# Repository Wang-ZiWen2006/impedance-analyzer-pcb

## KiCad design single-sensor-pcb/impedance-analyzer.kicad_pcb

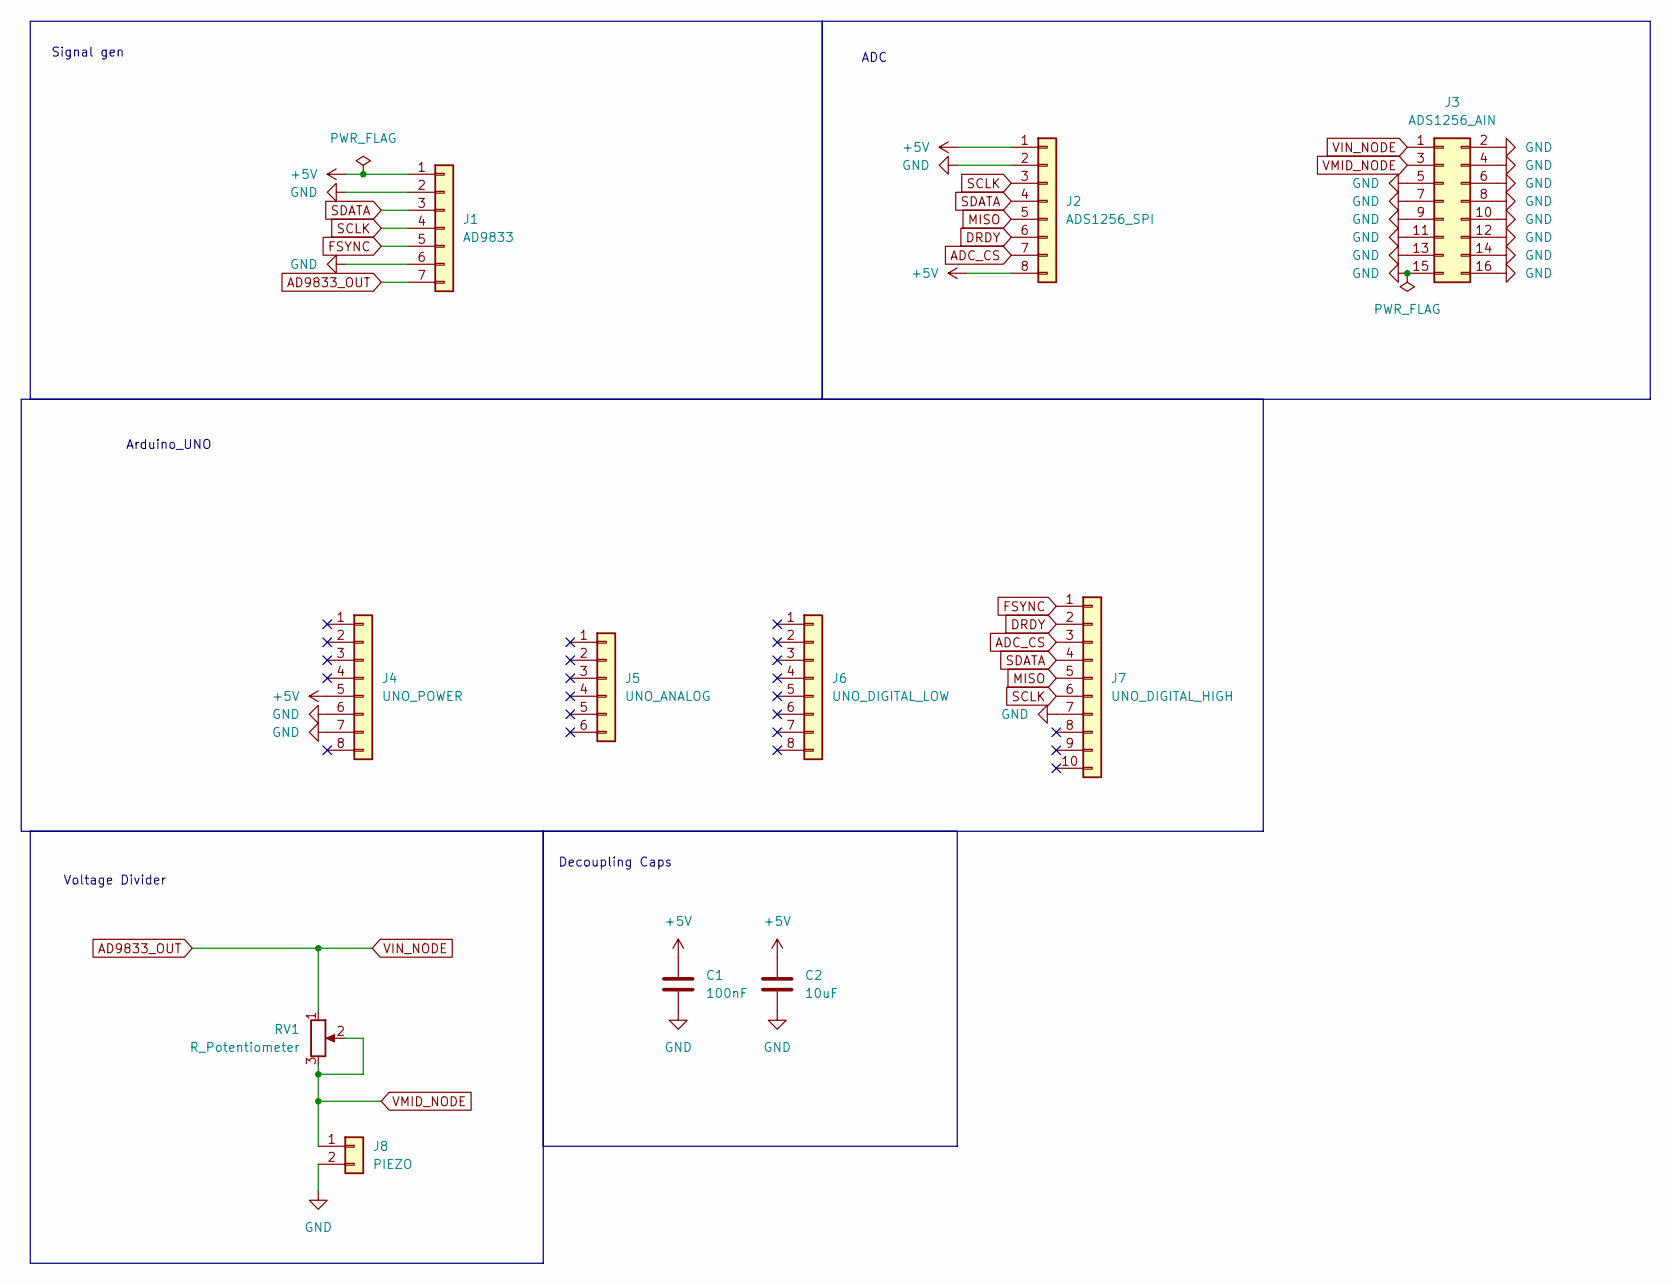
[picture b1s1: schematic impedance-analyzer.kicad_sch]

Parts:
C1: 100nF; C_Disc_D5.0mm_W2.5mm_P5.00mm
C2: 10uF; C_Disc_D5.0mm_W2.5mm_P5.00mm
J1: AD9833; PinSocket_1x07_P2.54mm_Vertical
J2: ADS1256_SPI; PinSocket_1x08_P2.54mm_Vertical
J3: ADS1256_AIN; PinSocket_2x08_P2.54mm_Vertical
J4: UNO_POWER; PinHeader_1x08_P2.54mm_Vertical
J5: UNO_ANALOG; PinHeader_1x06_P2.54mm_Vertical
J6: UNO_DIGITAL_LOW; PinHeader_1x08_P2.54mm_Vertical
J7: UNO_DIGITAL_HIGH; PinHeader_1x10_P2.54mm_Vertical
J8: PIEZO; TerminalBlock_Phoenix_MPT-0,5-2-2.54_1x02_P2.54mm_Horizontal
RV1: R_Potentiometer; Potentiometer_Bourns_3296W_Vertical

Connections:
+5V: C1.1, C2.1, J1.1, J2.1, J2.8, J4.5
AD9833_OUT: J1.7, J3.1, RV1.1
ADC_CS: J2.7, J7.3
DRDY: J2.6, J7.2
FSYNC: J1.5, J7.1
GND: C1.2, C2.2, J1.2, J1.6, J2.2, J3.2, J3.4, J3.5, J3.6, J3.7, J3.8, J3.9, J3.10, J3.11, J3.12, J3.13, J3.14, J3.15, J3.16, J4.6, J4.7, J7.7, J8.2
MISO: J2.5, J7.5
SCLK: J1.4, J2.3, J7.6
SDATA: J1.3, J2.4, J7.4
VMID_NODE: J3.3, J8.1, RV1.2, RV1.3

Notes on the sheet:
ADC
Voltage Divider
Signal gen
Decoupling Caps
Arduino_UNO

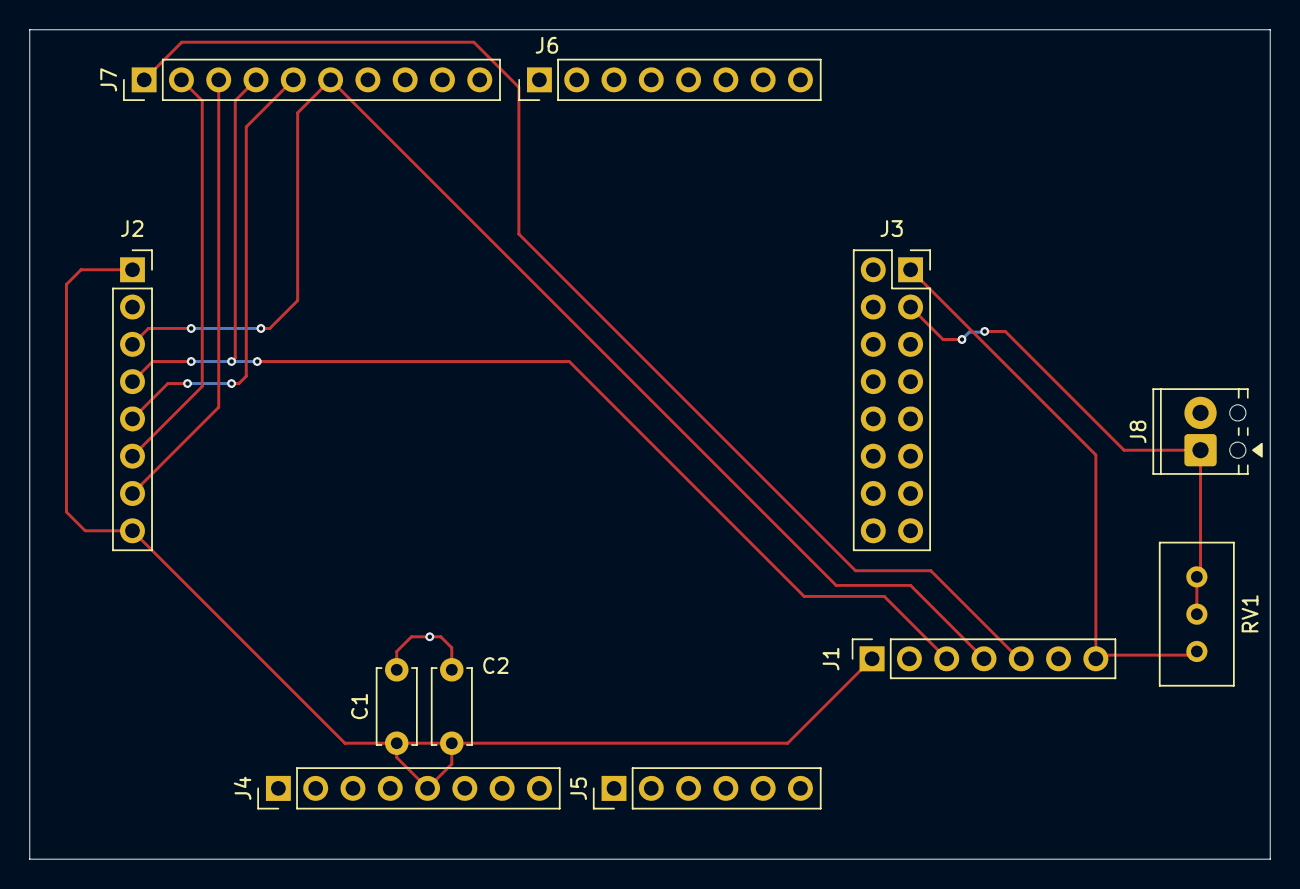
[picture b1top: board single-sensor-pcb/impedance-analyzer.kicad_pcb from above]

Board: 2 copper layers, 84.5 x 56.5 mm, 11 parts (0 on the bottom side), 10 nets.

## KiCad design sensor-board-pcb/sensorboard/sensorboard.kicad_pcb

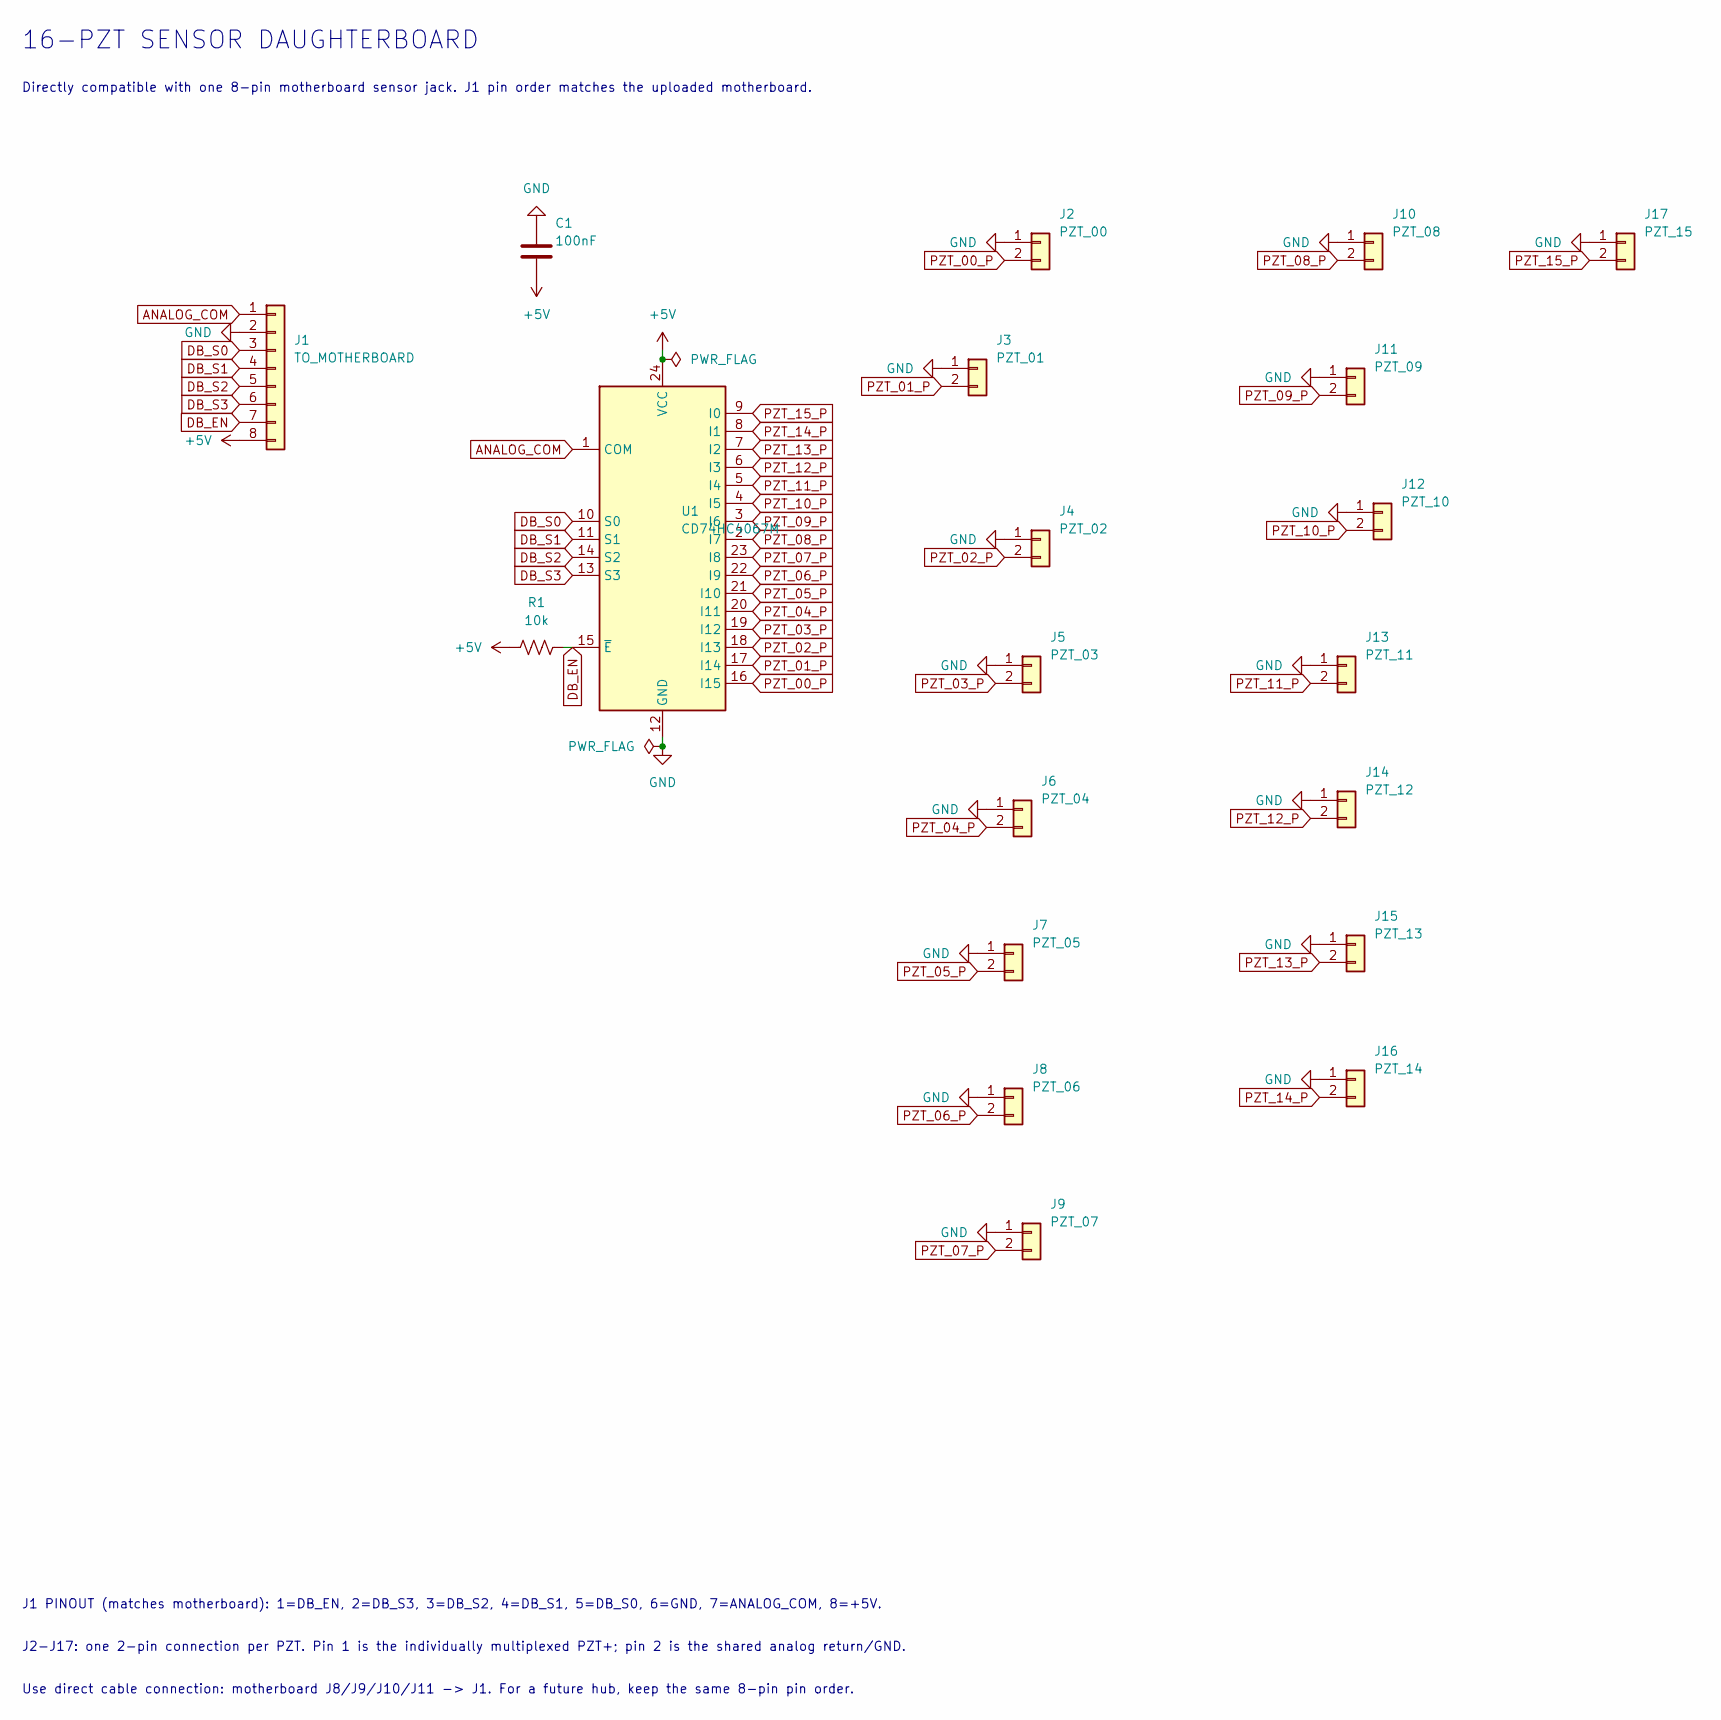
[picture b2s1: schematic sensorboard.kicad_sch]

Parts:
C1: 100nF; C_Disc_D5.0mm_W2.5mm_P5.00mm
J1: TO_MOTHERBOARD; Molex_Micro-Fit_3.0_43650-0815_1x08_P3.00mm_Vertical
J2: PZT_00; PinHeader_1x02_P2.54mm_Vertical
J3: PZT_01; PinHeader_1x02_P2.54mm_Vertical
J4: PZT_02; PinHeader_1x02_P2.54mm_Vertical
J5: PZT_03; PinHeader_1x02_P2.54mm_Vertical
J6: PZT_04; PinHeader_1x02_P2.54mm_Vertical
J7: PZT_05; PinHeader_1x02_P2.54mm_Vertical
J8: PZT_06; PinHeader_1x02_P2.54mm_Vertical
J9: PZT_07; PinHeader_1x02_P2.54mm_Vertical
J10: PZT_08; PinHeader_1x02_P2.54mm_Vertical
J11: PZT_09; PinHeader_1x02_P2.54mm_Vertical
J12: PZT_10; PinHeader_1x02_P2.54mm_Vertical
J13: PZT_11; PinHeader_1x02_P2.54mm_Vertical
J14: PZT_12; PinHeader_1x02_P2.54mm_Vertical
J15: PZT_13; PinHeader_1x02_P2.54mm_Vertical
J16: PZT_14; PinHeader_1x02_P2.54mm_Vertical
J17: PZT_15; PinHeader_1x02_P2.54mm_Vertical
R1: 10k; R_Axial_DIN0207_L6.3mm_D2.5mm_P7.62mm_Horizontal
U1: CD74HC4067M; DIP-24_W7.62mm

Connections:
+5V: C1.2, J1.8, R1.1, U1.24 (VCC)
ANALOG_COM: J1.1, U1.1 (COM)
DB_EN: J1.7, R1.2, U1.15 (~E)
DB_S0: J1.3, U1.10 (S0)
DB_S1: J1.4, U1.11 (S1)
DB_S2: J1.5, U1.14 (S2)
DB_S3: J1.6, U1.13 (S3)
GND: C1.1, J1.2, J2.1, J3.1, J4.1, J5.1, J6.1, J7.1, J8.1, J9.1, J10.1, J11.1, J12.1, J13.1, J14.1, J15.1, J16.1, J17.1, U1.12 (GND)
PZT_00_P: J2.2, U1.16 (I15)
PZT_01_P: J3.2, U1.17 (I14)
PZT_02_P: J4.2, U1.18 (I13)
PZT_03_P: J5.2, U1.19 (I12)
PZT_04_P: J6.2, U1.20 (I11)
PZT_05_P: J7.2, U1.21 (I10)
PZT_06_P: J8.2, U1.22 (I9)
PZT_07_P: J9.2, U1.23 (I8)
PZT_08_P: J10.2, U1.2 (I7)
PZT_09_P: J11.2, U1.3 (I6)
PZT_10_P: J12.2, U1.4 (I5)
PZT_11_P: J13.2, U1.5 (I4)
PZT_12_P: J14.2, U1.6 (I3)
PZT_13_P: J15.2, U1.7 (I2)
PZT_14_P: J16.2, U1.8 (I1)
PZT_15_P: J17.2, U1.9 (I0)

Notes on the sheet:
16-PZT SENSOR DAUGHTERBOARD
J1 PINOUT (matches motherboard): 1=DB_EN, 2=DB_S3, 3=DB_S2, 4=DB_S1, 5=DB_S0, 6=GND, 7=ANALOG_COM, 8=+5V.
Use direct cable connection: motherboard J8/J9/J10/J11 -> J1. For a future hub, keep the same 8-pin pin order.
J2-J17: one 2-pin connection per PZT. Pin 1 is the individually multiplexed PZT+; pin 2 is the shared analog return/GND.
Directly compatible with one 8-pin motherboard sensor jack. J1 pin order matches the uploaded motherboard.

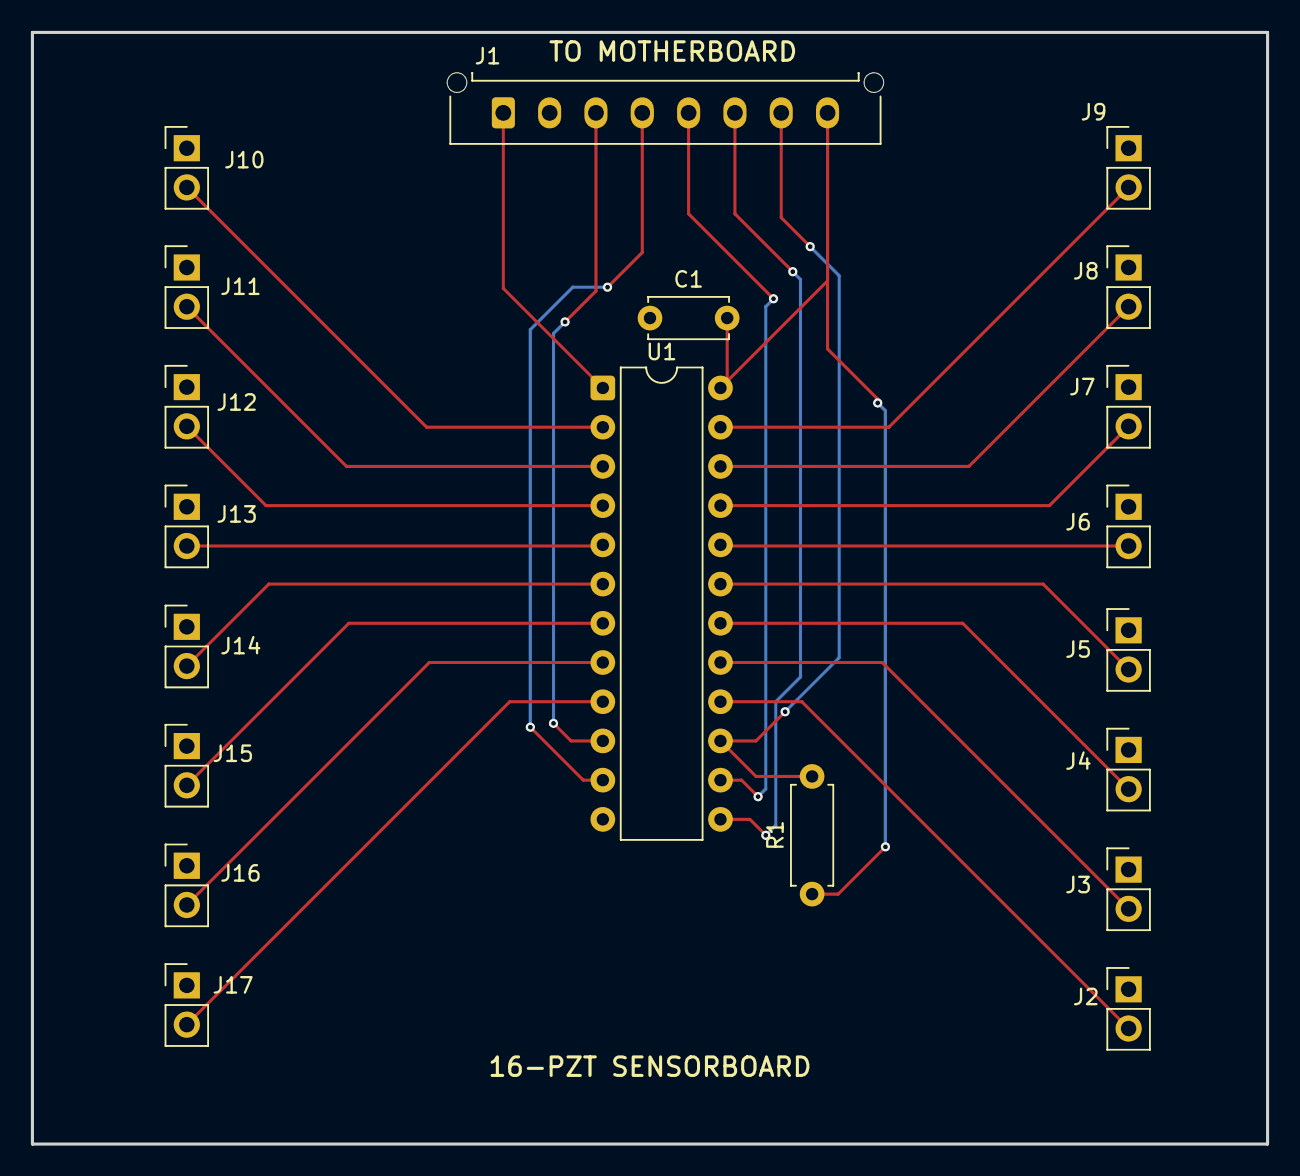
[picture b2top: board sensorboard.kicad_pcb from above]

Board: 2 copper layers, 80.0 x 72.0 mm, 20 parts (0 on the bottom side), 24 nets.

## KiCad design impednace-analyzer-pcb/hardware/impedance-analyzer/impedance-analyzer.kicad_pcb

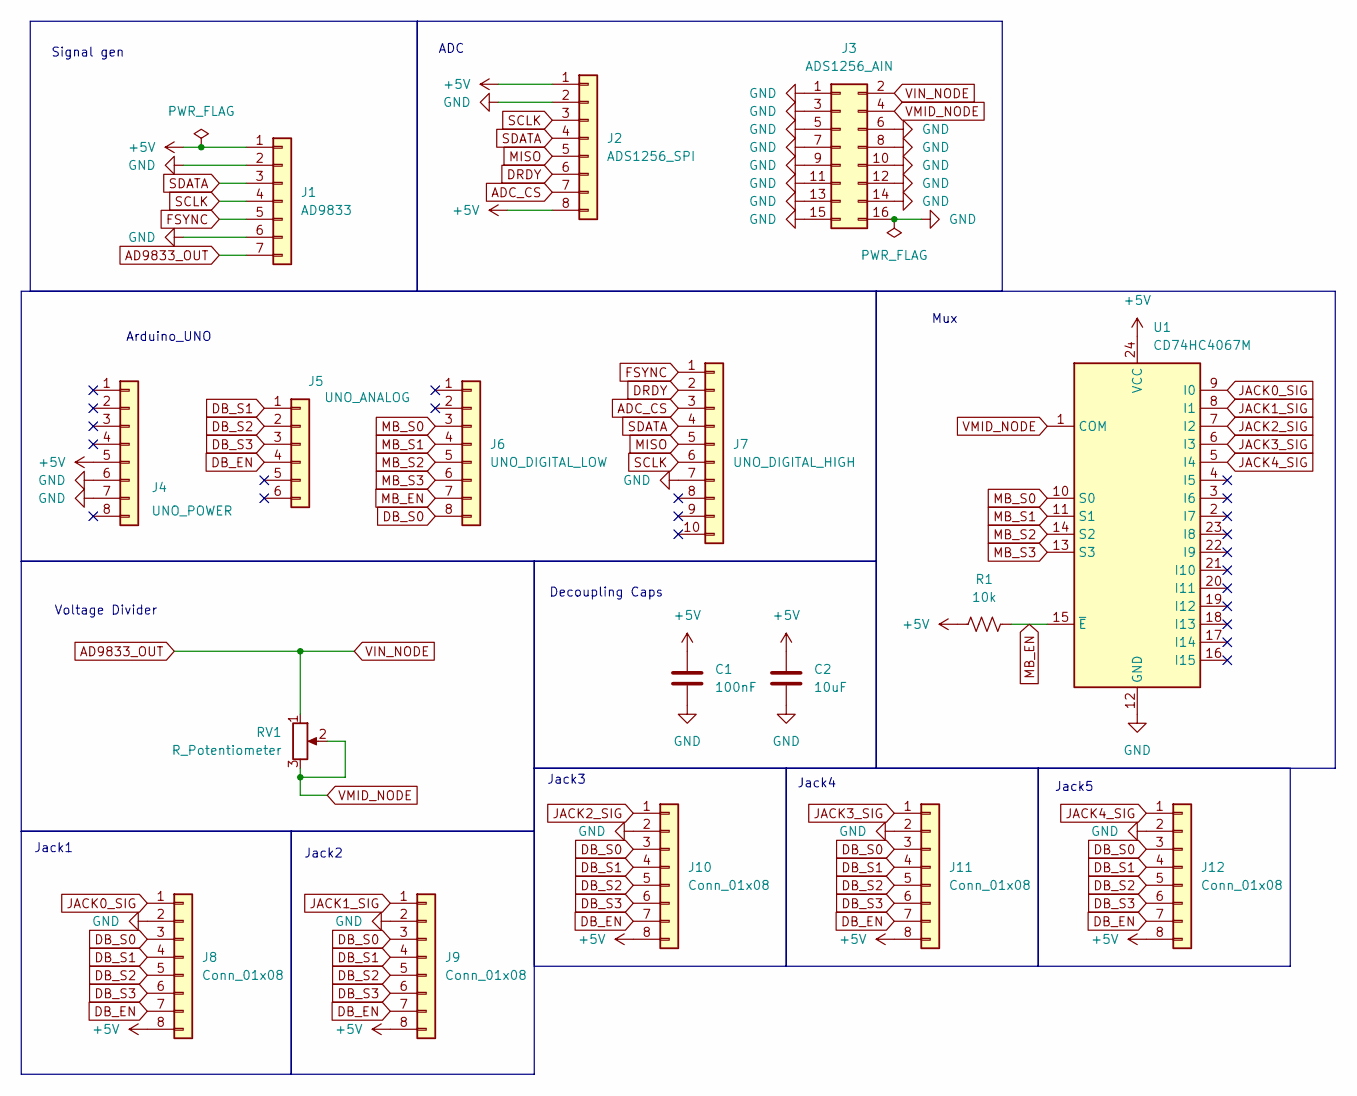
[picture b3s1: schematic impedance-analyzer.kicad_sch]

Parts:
C1: 100nF; C_0805_2012Metric_Pad1.18x1.45mm_HandSolder
C2: 10uF; C_0805_2012Metric_Pad1.18x1.45mm_HandSolder
J1: AD9833; PinSocket_1x07_P2.54mm_Vertical
J2: ADS1256_SPI; PinSocket_1x08_P2.54mm_Vertical
J3: ADS1256_AIN; PinSocket_2x08_P2.54mm_Vertical
J4: UNO_POWER; PinHeader_1x08_P2.54mm_Vertical
J5: UNO_ANALOG; PinHeader_1x06_P2.54mm_Vertical
J6: UNO_DIGITAL_LOW; PinHeader_1x08_P2.54mm_Vertical
J7: UNO_DIGITAL_HIGH; PinHeader_1x10_P2.54mm_Vertical
J8, J9, J10, J11, J12: Conn_01x08; Molex_Micro-Fit_3.0_43650-0815_1x08_P3.00mm_Vertical
R1: 10k; R_0805_2012Metric_Pad1.20x1.40mm_HandSolder
RV1: R_Potentiometer; Potentiometer_Bourns_3296W_Vertical
U1: CD74HC4067M; DIP-24_W7.62mm

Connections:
+5V: C1.1, C2.1, J1.1, J2.1, J2.8, J4.5, J8.8, J9.8, J10.8, J11.8, J12.8, R1.1, U1.24 (VCC)
AD9833_OUT: J1.7, J3.2, RV1.1
ADC_CS: J2.7, J7.3
DB_EN: J5.4, J8.7, J9.7, J10.7, J11.7, J12.7
DB_S0: J6.8, J8.3, J9.3, J10.3, J11.3, J12.3
DB_S1: J5.1, J8.4, J9.4, J10.4, J11.4, J12.4
DB_S2: J5.2, J8.5, J9.5, J10.5, J11.5, J12.5
DB_S3: J5.3, J8.6, J9.6, J10.6, J11.6, J12.6
DRDY: J2.6, J7.2
FSYNC: J1.5, J7.1
GND: C1.2, C2.2, J1.2, J1.6, J2.2, J3.1, J3.3, J3.5, J3.6, J3.7, J3.8, J3.9, J3.10, J3.11, J3.12, J3.13, J3.14, J3.15, J3.16, J4.6, J4.7, J7.7, J8.2, J9.2, J10.2, J11.2, J12.2, U1.12 (GND)
JACK0_SIG: J8.1, U1.9 (I0)
JACK1_SIG: J9.1, U1.8 (I1)
JACK2_SIG: J10.1, U1.7 (I2)
JACK3_SIG: J11.1, U1.6 (I3)
JACK4_SIG: J12.1, U1.5 (I4)
MB_EN: J6.7, R1.2, U1.15 (~E)
MB_S0: J6.3, U1.10 (S0)
MB_S1: J6.4, U1.11 (S1)
MB_S2: J6.5, U1.14 (S2)
MB_S3: J6.6, U1.13 (S3)
MISO: J2.5, J7.5
SCLK: J1.4, J2.3, J7.6
SDATA: J1.3, J2.4, J7.4
VMID_NODE: J3.4, RV1.2, RV1.3, U1.1 (COM)

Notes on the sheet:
Jack4
ADC
Voltage Divider
Signal gen
Jack1
Mux
Jack3
Decoupling Caps
Jack5
Jack2
Arduino_UNO

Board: 2 copper layers, 17 parts (0 on the bottom side), 25 nets, no tracks yet.

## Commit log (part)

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2026-03-30 added KiCad project files
2026-04-04 schematic work for AD9833
2026-06-22 added mux and jack to schematic
2026-06-25 updated schematic
